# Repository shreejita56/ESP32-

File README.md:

# ESP32-

So I made a simple Dev-board based on ESP32-S3-WROOM-1 . It has a USB-C for Communication and has all possible pin available on the Rp2040 . Boot/EN Pins 3.3V Voltage regulator on board LEDS . I tried to make it in a concise design. It was designed On kicad. 

## Features
- The Board uses USB-C for power and data transfer
- The Board is based on ESP32-S3-WROOM-1
- We have an onboard 3.3V Voltage regulator (AP63203WU)
- We also have EN/Boot pin for booting and uploading new firmware
- there is 2 set of 20 connector pins that connects to all possible pin outlets available on the MCU
- The PCB was Designed on Kicad
- It is Breadboard Compatible

## Schematcics

## PCB/CAD 

## Bill of Materials (BOM)

| Designation | Comment | Quantity | Total Price ($) | Link |
|---|---|---:|---:|---|
| C1 | 47uF | 2 | 1.2342 | [JLCPCB](https://jlcpcb.com/partdetail/152108-GRM188R60J476ME15D/C140782) |
| C2 | 10uF | 2 | 0.5440 | [JLCPCB](https://jlcpcb.com/partdetail/20411-CL10A106KP8NNNC/C19702) |
| C3 | 100nF | 2 | 0.1640 | [JLCPCB](https://jlcpcb.com/partdetail/YAGEO-CC0603KRX7R9BB104/C14663) |
| C4, C5 | 22uF | 4 | 0.6260 | [JLCPCB](https://jlcpcb.com/partdetail/60514-CL10A226MQ8NRNC/C59461) |
| D1 | LED | 2 | 0.3940 | [JLCPCB](https://jlcpcb.com/partdetail/90993-NCD0603Y2/C89811) |
| J1 | USB_C_Receptacle_USB2.0_16P | 2 | 4.1336 | [JLCPCB](https://jlcpcb.com/partdetail/XKBConnection-USB31_TYPE_CFSABC/C2880583) |
| L1 | 4.7uH | 2 | 0.5020 | [JLCPCB](https://jlcpcb.com/partdetail/Sunlord-SDFL1608Q4R7KTF/C1034) |
| R1, R2 | 33 | 4 | 0.0480 | [JLCPCB](https://jlcpcb.com/partdetail/23867-0603WAF330JT5E/C23140) |
| R3, R4 | 5.1K | 4 | 0.0300 | [JLCPCB](https://jlcpcb.com/partdetail/23913-0603WAF5101T5E/C23186) |
| R7 | 1K | 2 | 0.0360 | [JLCPCB](https://jlcpcb.com/partdetail/21904-0603WAF1001T5E/C21190) |
| U2 | AP63203WU | 2 | 6.1155 | [JLCPCB](https://jlcpcb.com/partdetail/DiodesIncorporated-AP63203WU7/C780769) |
| U3 | ESP32-S3-WROOM-1 | 2 | 10.3502 | [JLCPCB](https://jlcpcb.com/partdetail/3522416-ESP32_S3_WROOM_1UN16R8/C3013946) |
| PCB Fabrication | PCB cost | 1 | 4.0000 | — |
| Shipping | Shipping fee | 1 | 11.8700 | — |
| Feeders Loading fee | Assembly service fee | 1 | 18.6000 | — |
| SMT Assembly | Assembly service fee | 1 | 0.8800 | — |
| X-Ray Inspection | Inspection fee | 1 | 3.3000 | — |
| Packaging fee | Packaging fee | 1 | 0.5000 | — |
| Special components fee | Special components fee | 1 | 0.0600 | — |
| **GRAND TOTAL** | **All components, PCB, shipping and fees** | — | **63.39** | — |

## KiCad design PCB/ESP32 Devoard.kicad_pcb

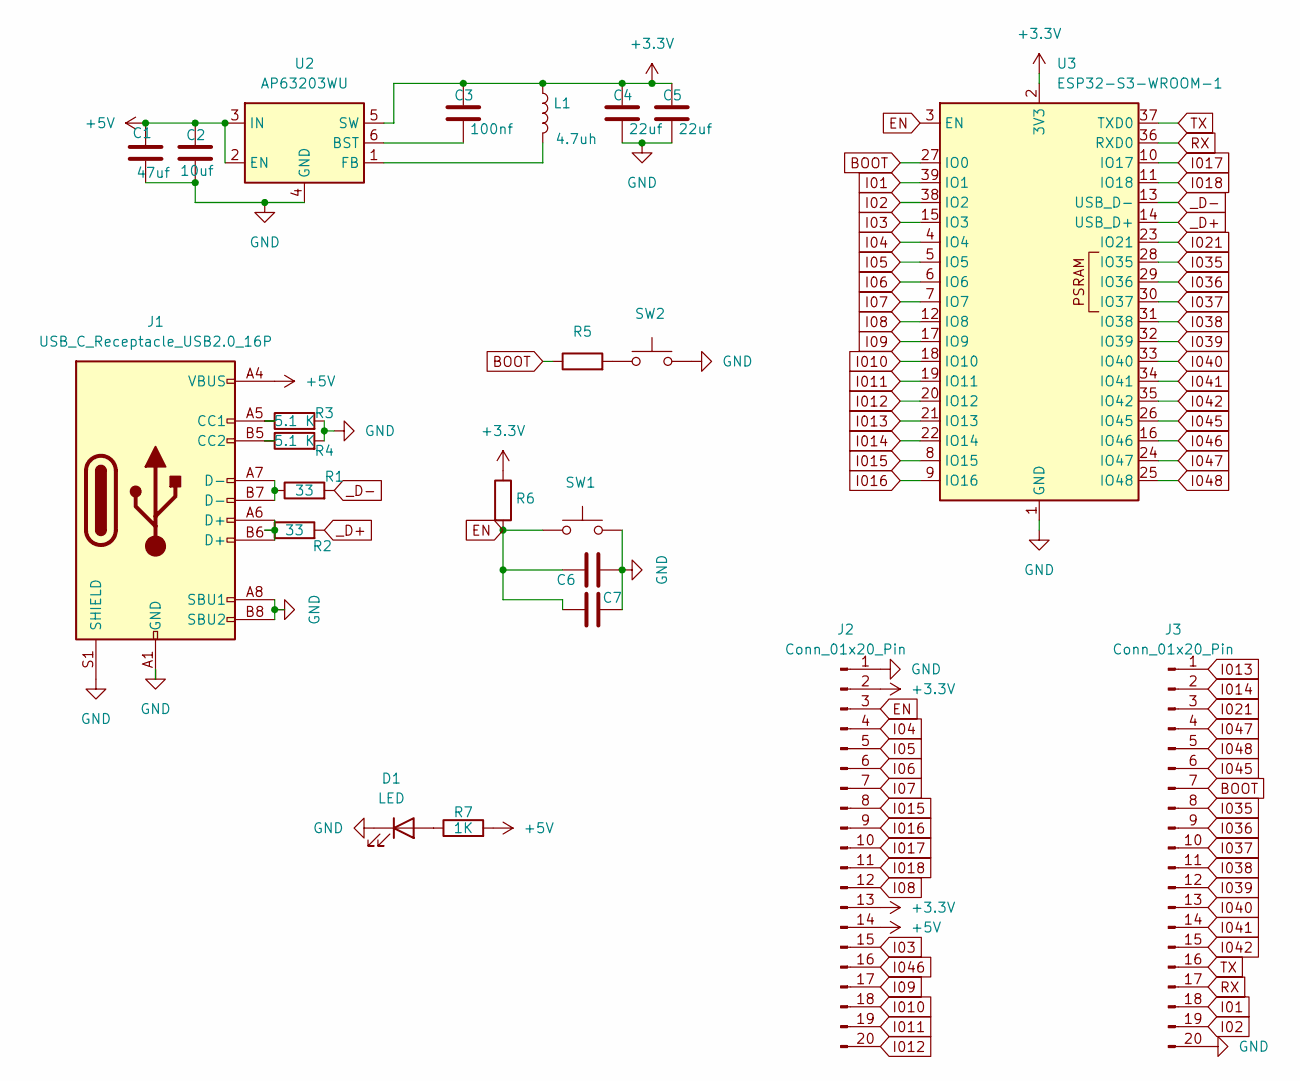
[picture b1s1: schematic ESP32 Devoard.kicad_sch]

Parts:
C1: 47uf; C_0603_1608Metric
C2: 10uf; C_0603_1608Metric
C3: 100nf; C_0603_1608Metric
C4, C5: 22uf; C_0603_1608Metric
C6, C7: C; C_0603_1608Metric
D1: LED; C_0603_1608Metric
J1: USB_C_Receptacle_USB2.0_16P; USB_C_Receptacle_G-Switch_GT-USB-7010ASV
J2, J3: Conn_01x20_Pin; PinHeader_1x20_P2.54mm_Vertical
L1: 4.7uh; L_0603_1608Metric
R1, R2: 33; R_0603_1608Metric
R3, R4: 5.1 K; R_0603_1608Metric
R5, R6: R; C_0603_1608Metric
R7: 1K; C_0603_1608Metric
SW1, SW2: SW_Push; SW_SPST_PTS810
U2: AP63203WU; TSOT-23-6
U3: ESP32-S3-WROOM-1

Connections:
+3.3V: C3.1, C4.1, C5.1, J2.2, J2.13, L1.1, R6.1, U2.5 (SW), U3.2 (3V3)
+5V: C1.1, C2.1, J1.A4 (VBUS), J1.A9 (VBUS), J1.B4 (VBUS), J1.B9 (VBUS), J2.14, R7.2, U2.2 (EN), U2.3 (IN)
BOOT: J3.7, R5.1, U3.27 (IO0)
EN: C6.1, C7.1, J2.3, R6.2, SW1.1, U3.3 (EN)
GND: C1.2, C2.2, C4.2, C5.2, C6.2, C7.2, D1.1 (K), J1.A1 (GND), J1.A8 (SBU1), J1.A12 (GND), J1.B1 (GND), J1.B8 (SBU2), J1.B12 (GND), J1.S1 (SHIELD), J1.SH, J2.1, J3.20, R3.2, R4.2, SW1.2, SW2.2, U2.4 (GND), U3.1 (GND), U3.40 (GND), U3.41 (GND)
I01: J3.18, U3.39 (IO1)
I02: J3.19, U3.38 (IO2)
I03: J2.15, U3.15 (IO3)
I04: J2.4, U3.4 (IO4)
I05: J2.5, U3.5 (IO5)
I06: J2.6, U3.6 (IO6)
I07: J2.7, U3.7 (IO7)
I08: J2.12, U3.12 (IO8)
I09: J2.17, U3.17 (IO9)
I010: J2.18, U3.18 (IO10)
I011: J2.19, U3.19 (IO11)
I012: J2.20, U3.20 (IO12)
I013: J3.1, U3.21 (IO13)
I014: J3.2, U3.22 (IO14)
I015: J2.8, U3.8 (IO15)
I016: J2.9, U3.9 (IO16)
I017: J2.10, U3.10 (IO17)
I018: J2.11, U3.11 (IO18)
I021: J3.3, U3.23 (IO21)
I035: J3.8, U3.28 (IO35)
I036: J3.9, U3.29 (IO36)
I037: J3.10, U3.30 (IO37)
I038: J3.11, U3.31 (IO38)
I039: J3.12, U3.32 (IO39)
I040: J3.13, U3.33 (IO40)
I041: J3.14, U3.34 (IO41)
I042: J3.15, U3.35 (IO42)
I045: J3.6, U3.26 (IO45)
I046: J2.16, U3.16 (IO46)
I047: J3.4, U3.24 (IO47)
I048: J3.5, U3.25 (IO48)
unnamed: D1.2 (A), R7.1
unnamed: J1.A5 (CC1), R3.1
unnamed: J1.B5 (CC2), R4.1
unnamed: J1.A6 (D+), J1.B6 (D+), R2.1
unnamed: J1.A7 (D-), J1.B7 (D-), R1.1
unnamed: R5.2, SW2.1
unnamed: C3.2, U2.6 (BST)
unnamed: L1.2, U2.1 (FB)
RX: J3.17, U3.36 (RXD0)
TX: J3.16, U3.37 (TXD0)
_D+: R2.2, U3.14 (USB_D+)
_D-: R1.2, U3.13 (USB_D-)

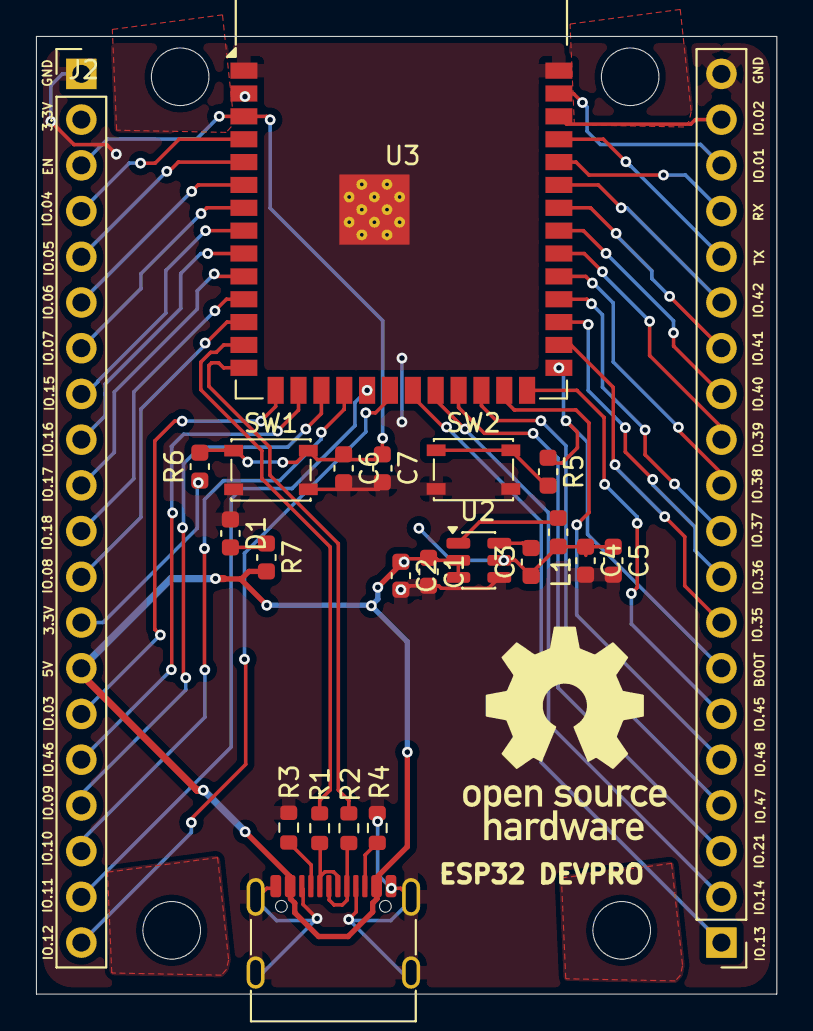
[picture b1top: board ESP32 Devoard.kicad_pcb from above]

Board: 2 copper layers, 41.1 x 53.2 mm, 23 parts (0 on the bottom side), 48 nets.

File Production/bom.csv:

Designator,Footprint,Quantity,Value,LCSC Part #
C1,0603,1,47uf,
C2,0603,1,10uf,
C3,0603,1,100nf,
"C4, C5",0603,2,22uf,
"C6, C7",0603,2,C,
D1,0603,1,LED,
J1,USB_C_Receptacle_G-Switch_GT-USB-7010ASV,1,USB_C_Receptacle_USB2.0_16P,
"J2, J3",PinHeader_1x20_P2.54mm_Vertical,2,Conn_01x20_Pin,
L1,0603,1,4.7uh,
"R1, R2",0603,2,33,
"R3, R4",0603,2,5.1 K,
"R5, R6",0603,2,R,
R7,0603,1,1K,
"SW1, SW2",SW_SPST_PTS810,2,SW_Push,
U2,TSOT-23-6,1,AP63203WU,
U3,ESP32-S3-WROOM-1,1,ESP32-S3-WROOM-1,
